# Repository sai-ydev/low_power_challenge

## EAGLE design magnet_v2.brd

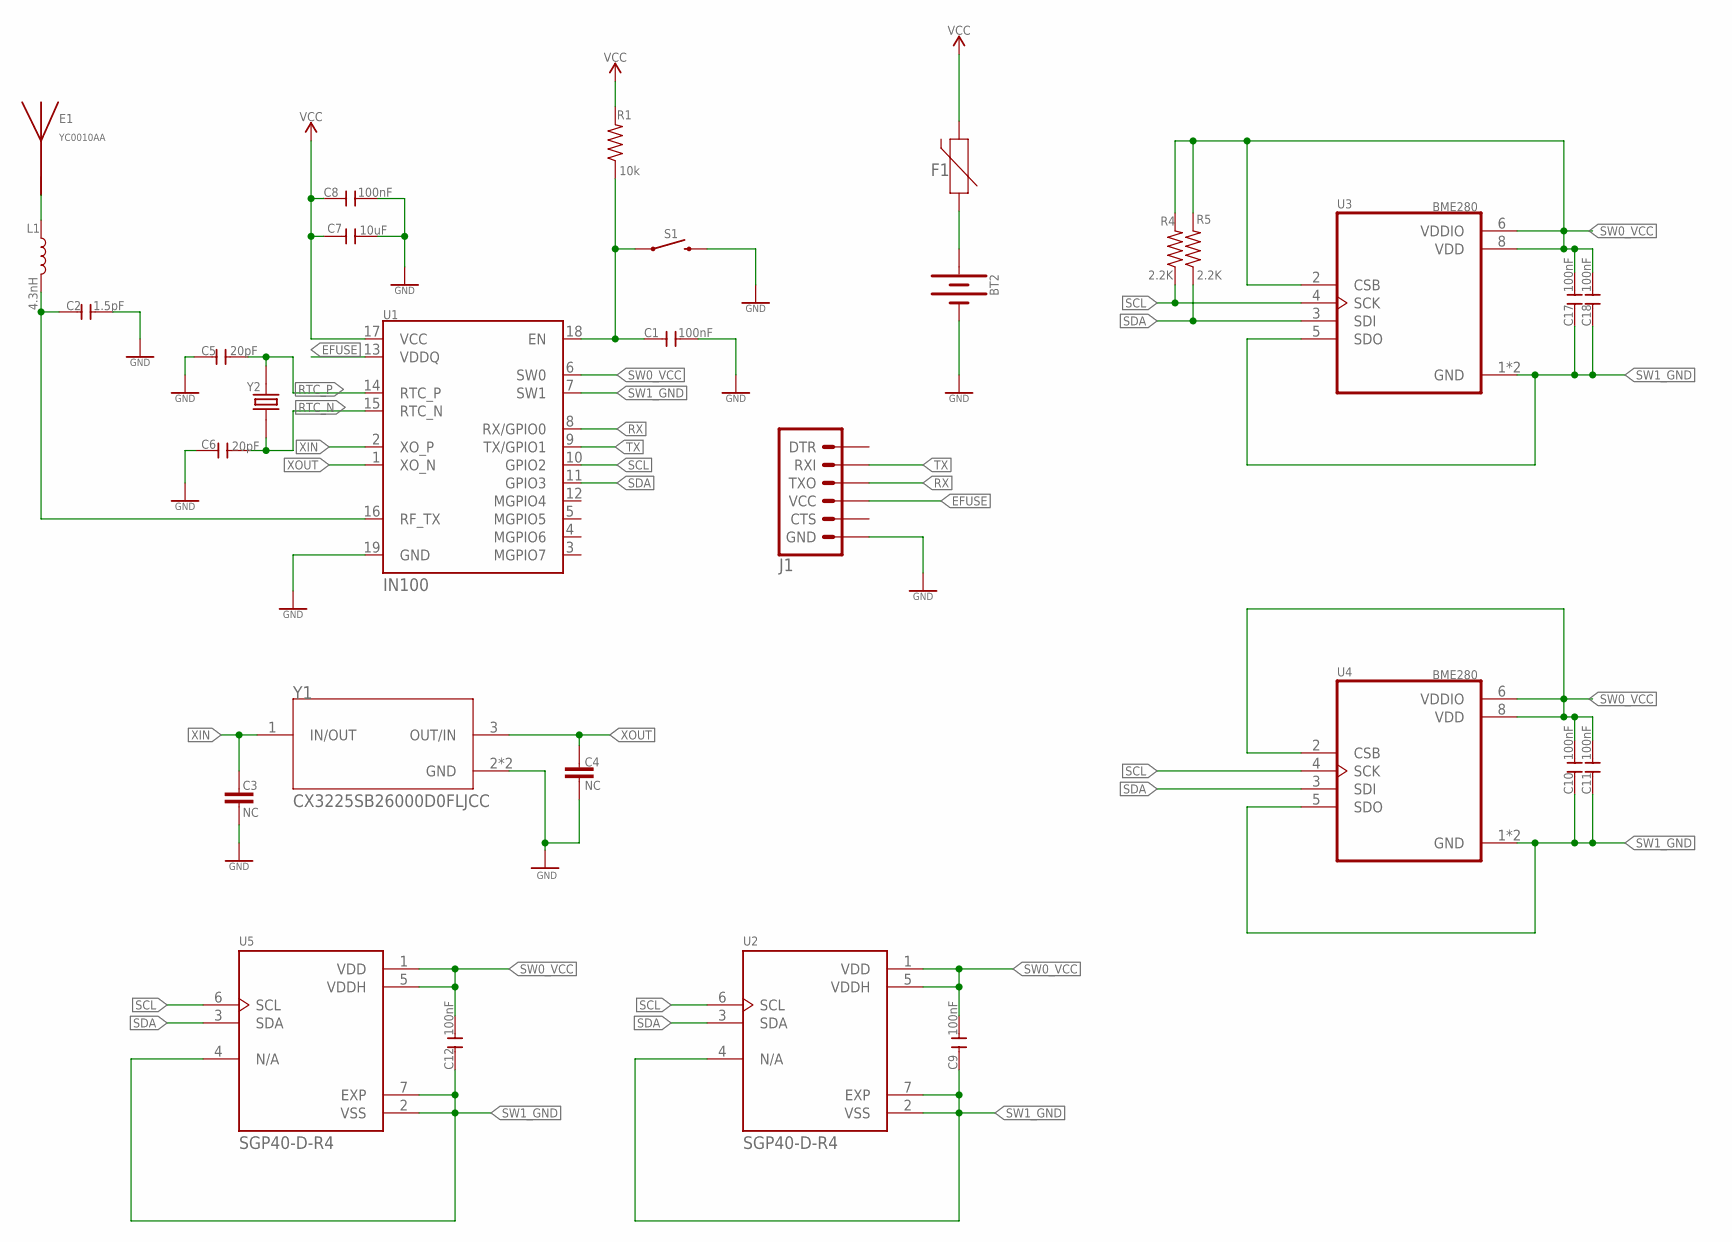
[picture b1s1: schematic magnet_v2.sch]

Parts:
BT2: BATTERY-12MM_SMD; BATTCON_12MM
C1, C8, C9, C10, C11, C12, C17, C18: 100nF; C0603
C2: 1.5pF; C0603
C3, C4: NC; 0603
C5, C6: 20pF; C0603
C7: 10uF; C0603
E1: YC0010AA; XCVR_YC0010AA
F1: RESC3115X65N
J1: 6_PIN_SERIAL_TARGETSMD; 1X06-SMD_RA_MALE
L1: 4.3nH; 0603
R1: 10k; 0603
R4, R5: 2.2K; 0603
S1: MOMENTARY-SWITCH-SPST-SMD-4.6X2.8MM; TACTILE_SWITCH_SMD_4.6X2.8MM
U1: IN100
U2, U5: SGP40-D-R4; XCDR_SGP40-D-R4
U3, U4: BME280; PSON65P250X250X100-8N
Y1: CX3225SB26000D0FLJCC; XTAL_ECS-480-8-33B-CWY-TR3
Y2: ECS-.327-12.5-16-TR; XTAL_ECS-.327-12.5-16-TR

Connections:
EFUSE: J1.4 (VCC), U1.13 (VDDQ)
GND: BT2.GND (-), C1.2, C2.2, C3.2, C4.2, C5.1, C6.1, C7.2, C8.2, J1.6 (GND), S1.3 (2), S1.4 (2), U1.19 (GND), Y1.2 (GND), Y1.4 (GND)
unnamed: C2.1, L1.2, U1.16 (RF_TX)
unnamed: E1.1, L1.1
unnamed: C1.1, R1.1, S1.1, S1.2 (1), U1.18 (EN)
unnamed: BT2.PWR@1 (+), F1.1
RTC_N: C6.2, U1.15 (RTC_N), Y2.1
RTC_P: C5.2, U1.14 (RTC_P), Y2.2
RX: J1.3 (TXO), U1.8 (RX/GPIO0)
SCL: R4.1, U1.10 (GPIO2), U2.6 (SCL), U3.4 (SCK), U4.4 (SCK), U5.6 (SCL)
SDA: R5.1, U1.11 (GPIO3), U2.3 (SDA), U3.3 (SDI), U4.3 (SDI), U5.3 (SDA)
SW0_VCC: C9.2, C10.2, C11.2, C12.2, C17.2, C18.2, R4.2, R5.2, U1.6 (SW0), U2.1 (VDD), U2.5 (VDDH), U3.2 (CSB), U3.6 (VDDIO), U3.8 (VDD), U4.2 (CSB), U4.6 (VDDIO), U4.8 (VDD), U5.1 (VDD), U5.5 (VDDH)
SW1_GND: C9.1, C10.1, C11.1, C12.1, C17.1, C18.1, U1.7 (SW1), U2.2 (VSS), U2.4 (N/A), U2.7 (EXP), U3.1 (GND), U3.5 (SDO), U3.7 (GND), U4.1 (GND), U4.5 (SDO), U4.7 (GND), U5.2 (VSS), U5.4 (N/A), U5.7 (EXP)
TX: J1.2 (RXI), U1.9 (TX/GPIO1)
VCC: C7.1, C8.1, F1.2, R1.2, U1.17 (VCC)
XIN: C3.1, U1.2 (XO_P), Y1.1 (IN/OUT)
XOUT: C4.1, U1.1 (XO_N), Y1.3 (OUT/IN)

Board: 4 copper layers, 30 parts (5 on the bottom side), 17 nets, no tracks yet.

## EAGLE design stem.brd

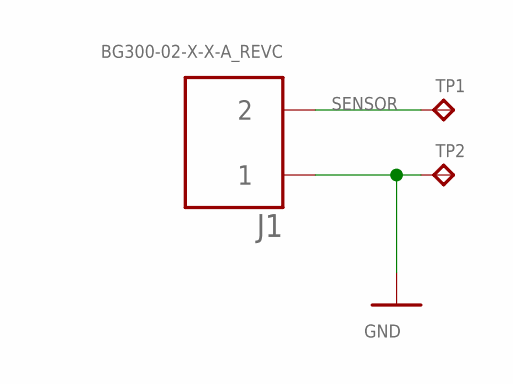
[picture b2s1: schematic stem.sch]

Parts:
J1: BG300-02-X-X-A_REVC; GCT_BG300-02-X-X-A_REVC
TP1, TP2: TPB1,27; B1,27

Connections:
GND: J1.1, TP2.TP
SENSOR: J1.2, TP1.TP

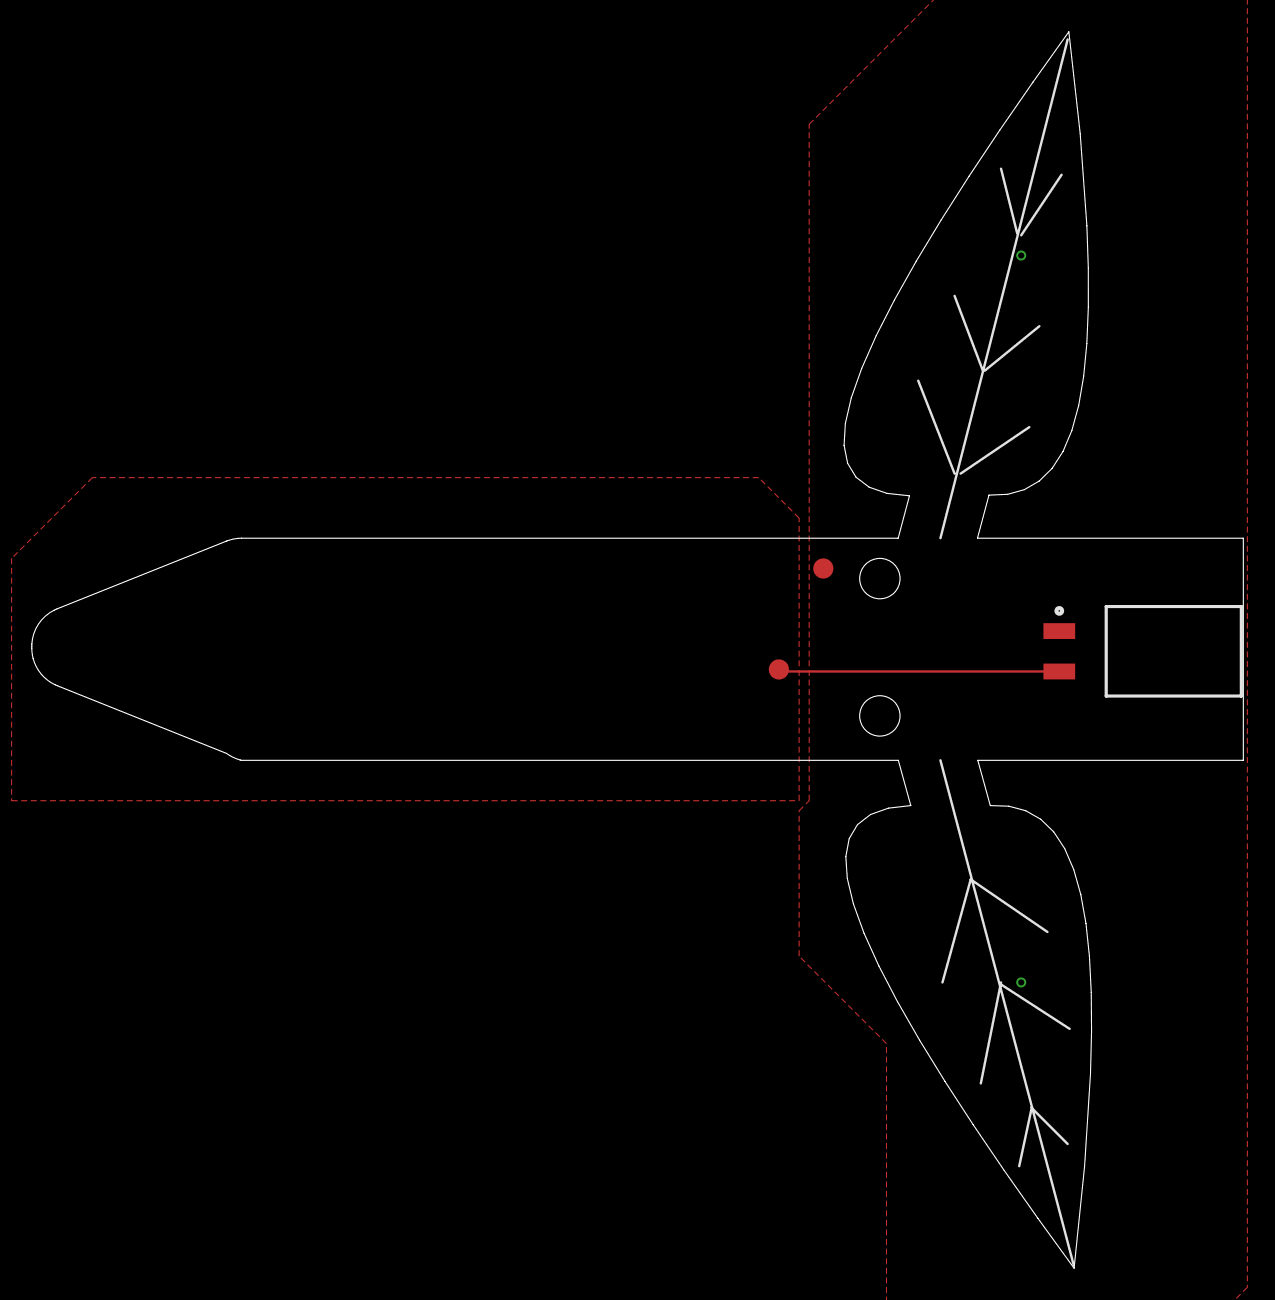
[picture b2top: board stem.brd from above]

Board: 2 copper layers, 76.2 x 77.8 mm, 3 parts (0 on the bottom side), 2 nets.

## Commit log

2023-03-07 Check-in
2023-03-07 fridge_magnet pcb files
2023-03-10 File check-in
2023-04-12 v2 board

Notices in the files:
parts and their libraries:
SparkFun-Batteries: Licensing: Creative Commons ShareAlike 4.0 International - https://creativecommons.org/licenses/by-sa/4.0
